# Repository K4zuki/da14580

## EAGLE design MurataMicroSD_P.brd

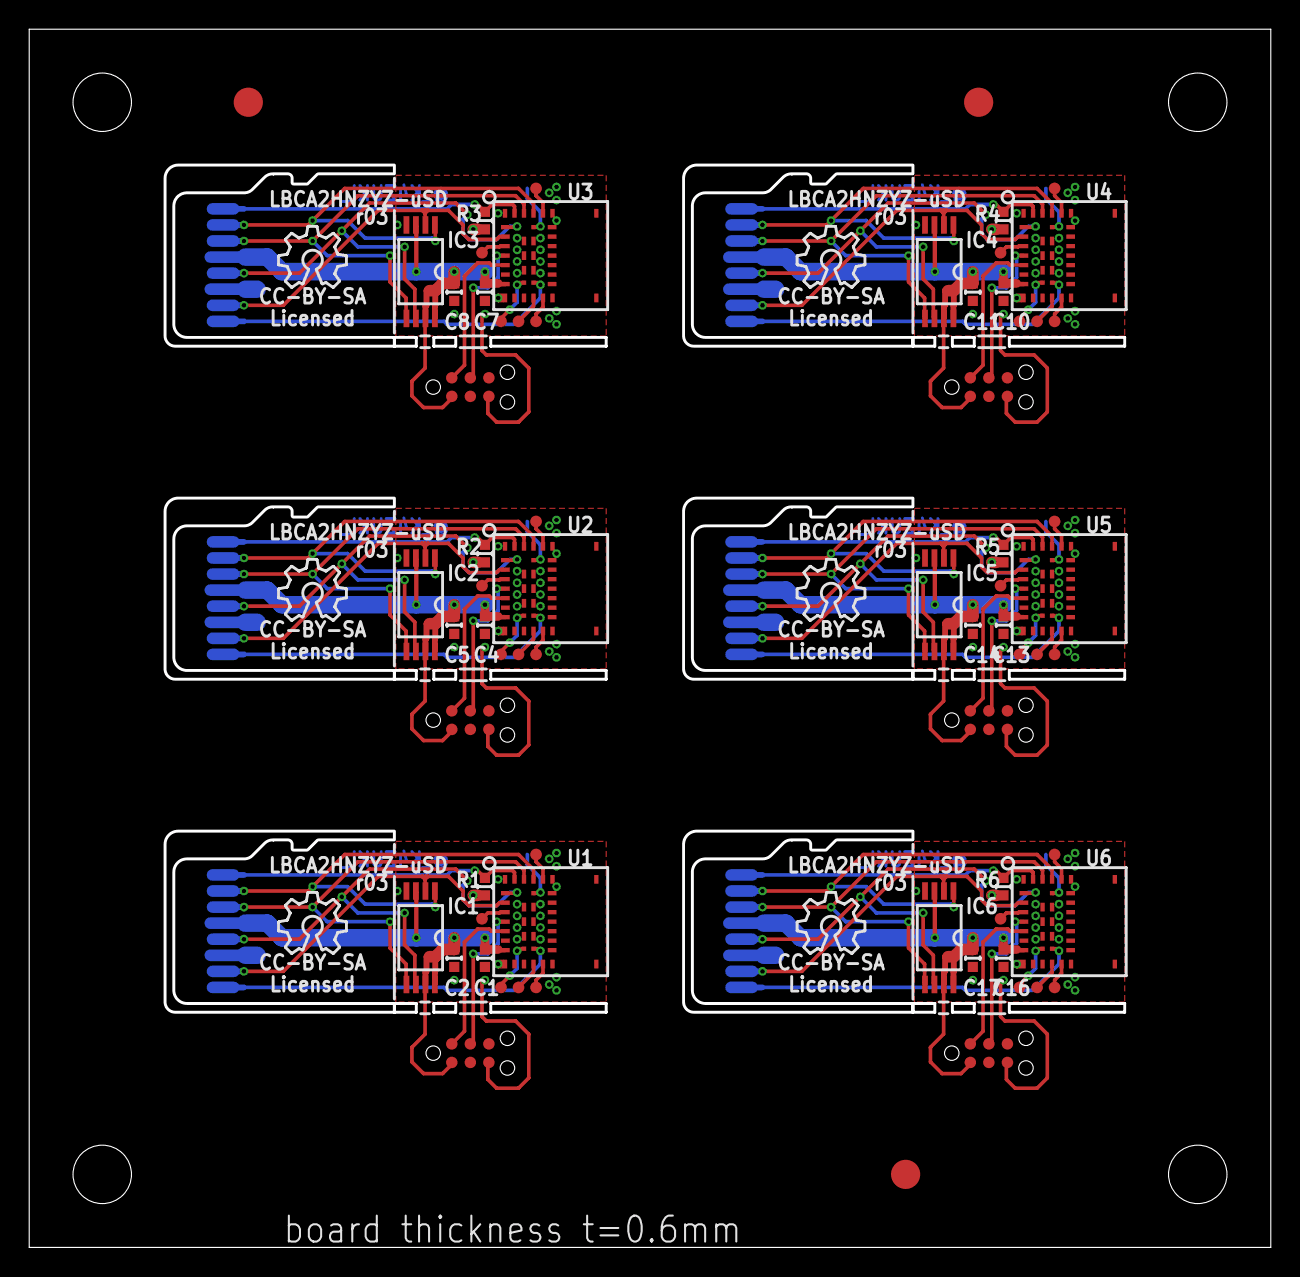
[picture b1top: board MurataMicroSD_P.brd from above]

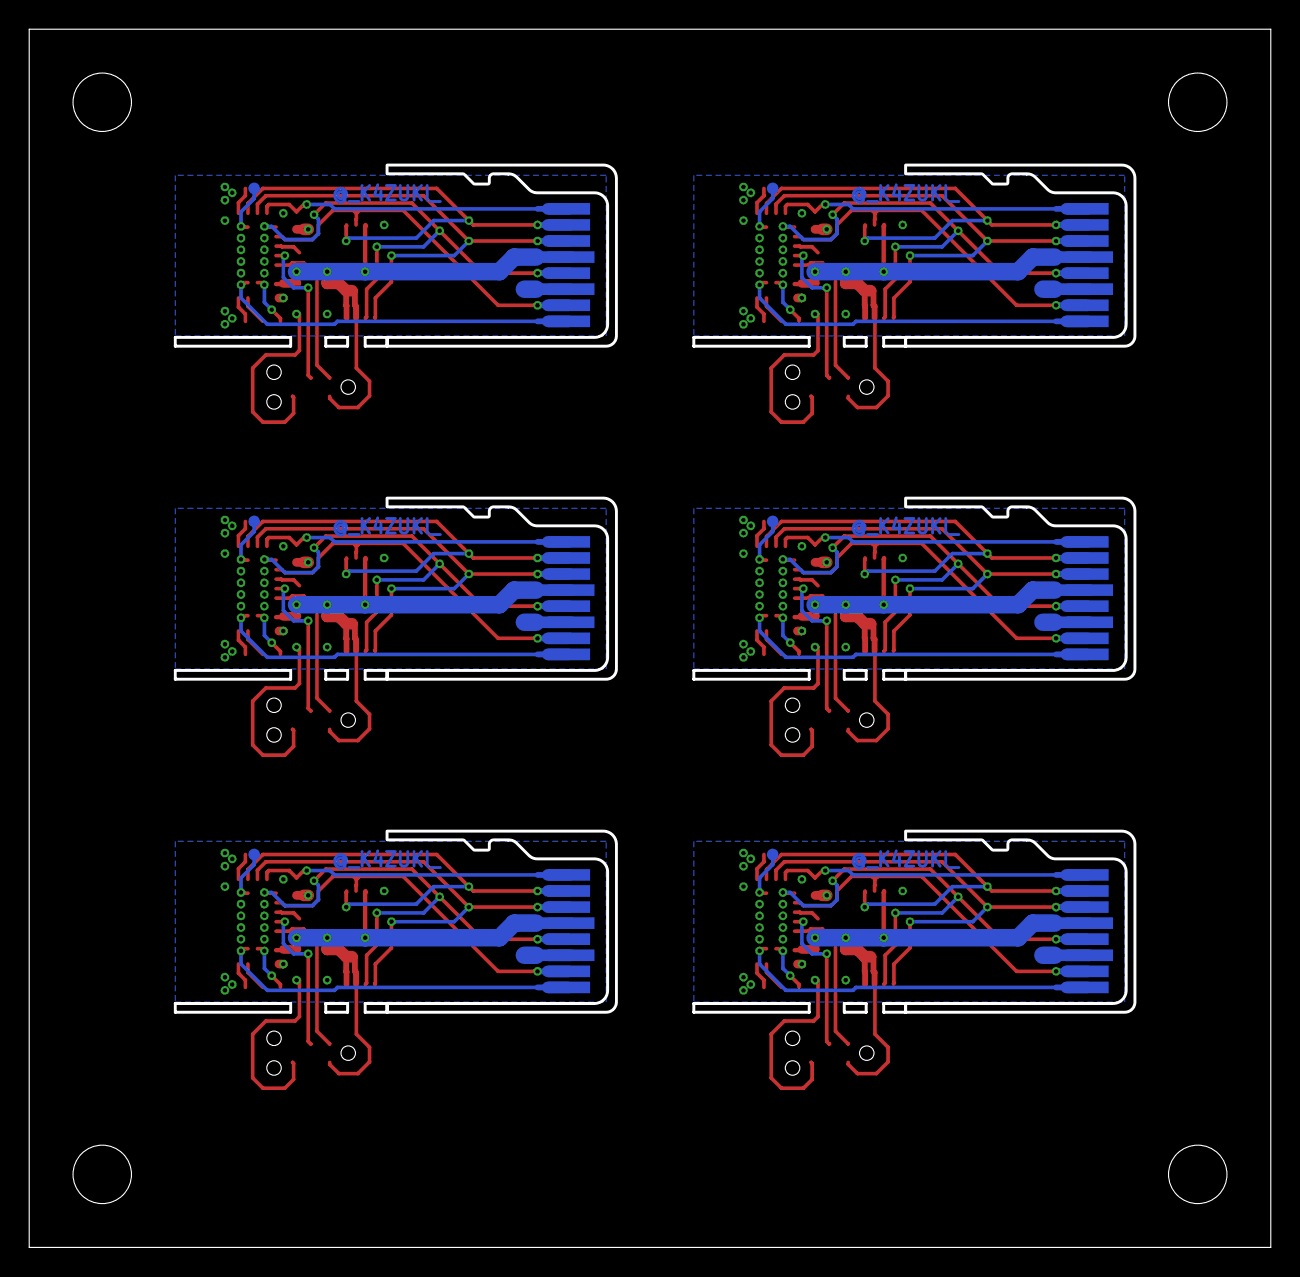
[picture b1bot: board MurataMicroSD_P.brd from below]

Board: 2 copper layers, 85.0 x 83.4 mm, 87 parts (12 on the bottom side), 96 nets.

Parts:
C1, C2, C4, C5, C7, C8, C10, C11, C13, C14, C16, C17: C0402
C3, C6, C9, C12, C15, C100: BOARD_MICROSD
CON1, CON2, CON3, CON4, CON5, CON6: CON_TC2030-CTL-NL; CON_TC2030-IDC-NL
IC1, IC2, IC3, IC4, IC5, IC6: 1265-1139-1-ND; IC_08_0.65_160MIL
R1, R2, R3, R4, R5, R6: C0402
TP1, TP2, TP3, TP4, TP5, TP6, TP7, TP8, TP9, TP10, TP11, TP12, TP13, TP14, TP15, TP16, TP17, TP18, TP19, TP20, TP21, TP22, TP23, TP24, TP25, TP26, TP27, TP28, TP29, TP30, TP31, TP32, TP33, TP34, TP35, TP36: TPTP08R; TP08R
TP100, TP101, TP102: TPTP20R; TP20R
U1, U2, U3, U4, U5, U6: IC_BLE_LBCA2HNZYZ-711; IC_MURATA_LBCA2HNZYZ-711
U$1, U$2, U$3, U$4, U$5, U$6: ICON_OSHW

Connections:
3.3V: C1.1, C2.1, C100.4_VDD, CON1.1, IC1.3, IC1.7, IC1.8, U1.7
3.3V1: C3.4_VDD, C4.1, C5.1, CON2.1, IC2.3, IC2.7, IC2.8, U2.7
3.3V2: C6.4_VDD, C7.1, C8.1, CON3.1, IC3.3, IC3.7, IC3.8, U3.7
3.3V3: C9.4_VDD, C10.1, C11.1, CON4.1, IC4.3, IC4.7, IC4.8, U4.7
3.3V4: C12.4_VDD, C13.1, C14.1, CON5.1, IC5.3, IC5.7, IC5.8, U5.7
3.3V5: C15.4_VDD, C16.1, C17.1, CON6.1, IC6.3, IC6.7, IC6.8, U6.7
!CS!: C100.2_CS, IC1.1, U1.23
!CS!1: C3.2_CS, IC2.1, U2.23
!CS!2: C6.2_CS, IC3.1, U3.23
!CS!3: C9.2_CS, IC4.1, U4.23
!CS!4: C12.2_CS, IC5.1, U5.23
!CS!5: C15.2_CS, IC6.1, U6.23
GND: C1.2, C2.2, C100.6_VSS, CON1.5, IC1.4, R1.1, U1.6, U1.8, U1.15, U1.16, U1.17, U1.18, U1.20, U1.21, U1.26, U1.27, U1.28, U1.29, U1.32, U1.33, U1.34
GND1: C3.6_VSS, C4.2, C5.2, CON2.5, IC2.4, R2.1, U2.6, U2.8, U2.15, U2.16, U2.17, U2.18, U2.20, U2.21, U2.26, U2.27, U2.28, U2.29, U2.32, U2.33, U2.34
GND2: C6.6_VSS, C7.2, C8.2, CON3.5, IC3.4, R3.1, U3.6, U3.8, U3.15, U3.16, U3.17, U3.18, U3.20, U3.21, U3.26, U3.27, U3.28, U3.29, U3.32, U3.33, U3.34
GND3: C9.6_VSS, C10.2, C11.2, CON4.5, IC4.4, R4.1, U4.6, U4.8, U4.15, U4.16, U4.17, U4.18, U4.20, U4.21, U4.26, U4.27, U4.28, U4.29, U4.32, U4.33, U4.34
GND4: C12.6_VSS, C13.2, C14.2, CON5.5, IC5.4, R5.1, U5.6, U5.8, U5.15, U5.16, U5.17, U5.18, U5.20, U5.21, U5.26, U5.27, U5.28, U5.29, U5.32, U5.33, U5.34
GND5: C15.6_VSS, C16.2, C17.2, CON6.5, IC6.4, R6.1, U6.6, U6.8, U6.15, U6.16, U6.17, U6.18, U6.20, U6.21, U6.26, U6.27, U6.28, U6.29, U6.32, U6.33, U6.34
MISO: C100.7_MISO, IC1.2, U1.2
MISO1: C3.7_MISO, IC2.2, U2.2
MISO2: C6.7_MISO, IC3.2, U3.2
MISO3: C9.7_MISO, IC4.2, U4.2
MISO4: C12.7_MISO, IC5.2, U5.2
MISO5: C15.7_MISO, IC6.2, U6.2
unnamed: C100.1_DAT2, R1.2, U1.25
unnamed: C3.1_DAT2, R2.2, U2.25
unnamed: C6.1_DAT2, R3.2, U3.25
unnamed: C9.1_DAT2, R4.2, U4.25
unnamed: C12.1_DAT2, R5.2, U5.25
unnamed: C15.1_DAT2, R6.2, U6.25
P0_1: TP9.TP, U1.22
P0_2: TP8.TP, U1.12
P0_3: TP7.TP, U1.11
P0_4: TP12.TP, U2.3
P0_5: TP2.TP, U2.11
P0_6: TP1.TP, U1.3
P0_7: TP3.TP, U2.12
P0_8: TP4.TP, U2.22
P0_9: TP18.TP, U3.3
P0_10: TP13.TP, U3.11
P0_11: TP14.TP, U3.12
P0_12: TP15.TP, U3.22
P0_13: TP24.TP, U4.3
P0_14: TP19.TP, U4.11
P0_15: TP20.TP, U4.12
P0_16: TP21.TP, U4.22
P0_17: TP30.TP, U5.3
P0_18: TP25.TP, U5.11
P0_19: TP26.TP, U5.12
P0_20: TP27.TP, U5.22
P0_21: TP36.TP, U6.3
P0_22: TP31.TP, U6.11
P0_23: TP32.TP, U6.12
P0_24: TP33.TP, U6.22
P1_0: TP10.TP, U1.35
P1_1: TP11.TP, U1.30
P1_2: TP5.TP, U2.35
P1_3: TP6.TP, U2.30
P1_4: TP16.TP, U3.35
P1_5: TP17.TP, U3.30
P1_6: TP22.TP, U4.35
P1_7: TP23.TP, U4.30
P1_8: TP28.TP, U5.35
P1_9: TP29.TP, U5.30
P1_10: TP34.TP, U6.35
P1_11: TP35.TP, U6.30
RXD_MOSI: C100.3_MOSI, IC1.5, U1.24
RXD_MOSI1: C3.3_MOSI, IC2.5, U2.24
RXD_MOSI2: C6.3_MOSI, IC3.5, U3.24
RXD_MOSI3: C9.3_MOSI, IC4.5, U4.24
RXD_MOSI4: C12.3_MOSI, IC5.5, U5.24
RXD_MOSI5: C15.3_MOSI, IC6.5, U6.24
SCK: C100.5_CLK, IC1.6, U1.1
SCK1: C3.5_CLK, IC2.6, U2.1
SCK2: C6.5_CLK, IC3.6, U3.1
SCK3: C9.5_CLK, IC4.6, U4.1
SCK4: C12.5_CLK, IC5.6, U5.1
SCK5: C15.5_CLK, IC6.6, U6.1
SWCLK: CON1.4, U1.4
SWCLK1: CON2.4, U2.4
SWCLK2: CON3.4, U3.4
SWCLK3: CON4.4, U4.4
SWCLK4: CON5.4, U5.4
SWCLK5: CON6.4, U6.4
SWDIO: CON1.2, U1.5
SWDIO1: CON2.2, U2.5
SWDIO2: CON3.2, U3.5
SWDIO3: CON4.2, U4.5
SWDIO4: CON5.2, U5.5
SWDIO5: CON6.2, U6.5
VPP: C100.8_DAT1, U1.31
VPP1: C3.8_DAT1, U2.31
VPP2: C6.8_DAT1, U3.31
VPP3: C9.8_DAT1, U4.31
VPP4: C12.8_DAT1, U5.31
VPP5: C15.8_DAT1, U6.31

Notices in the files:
MurataMicroSD_P.brd:
CC-BY-SA
